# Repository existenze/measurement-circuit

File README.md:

# measurement-circuit
Measurement Circuit design for Plasma Frontiers General Atomics DIII-D Neutral Beam injector upgrade projectproject

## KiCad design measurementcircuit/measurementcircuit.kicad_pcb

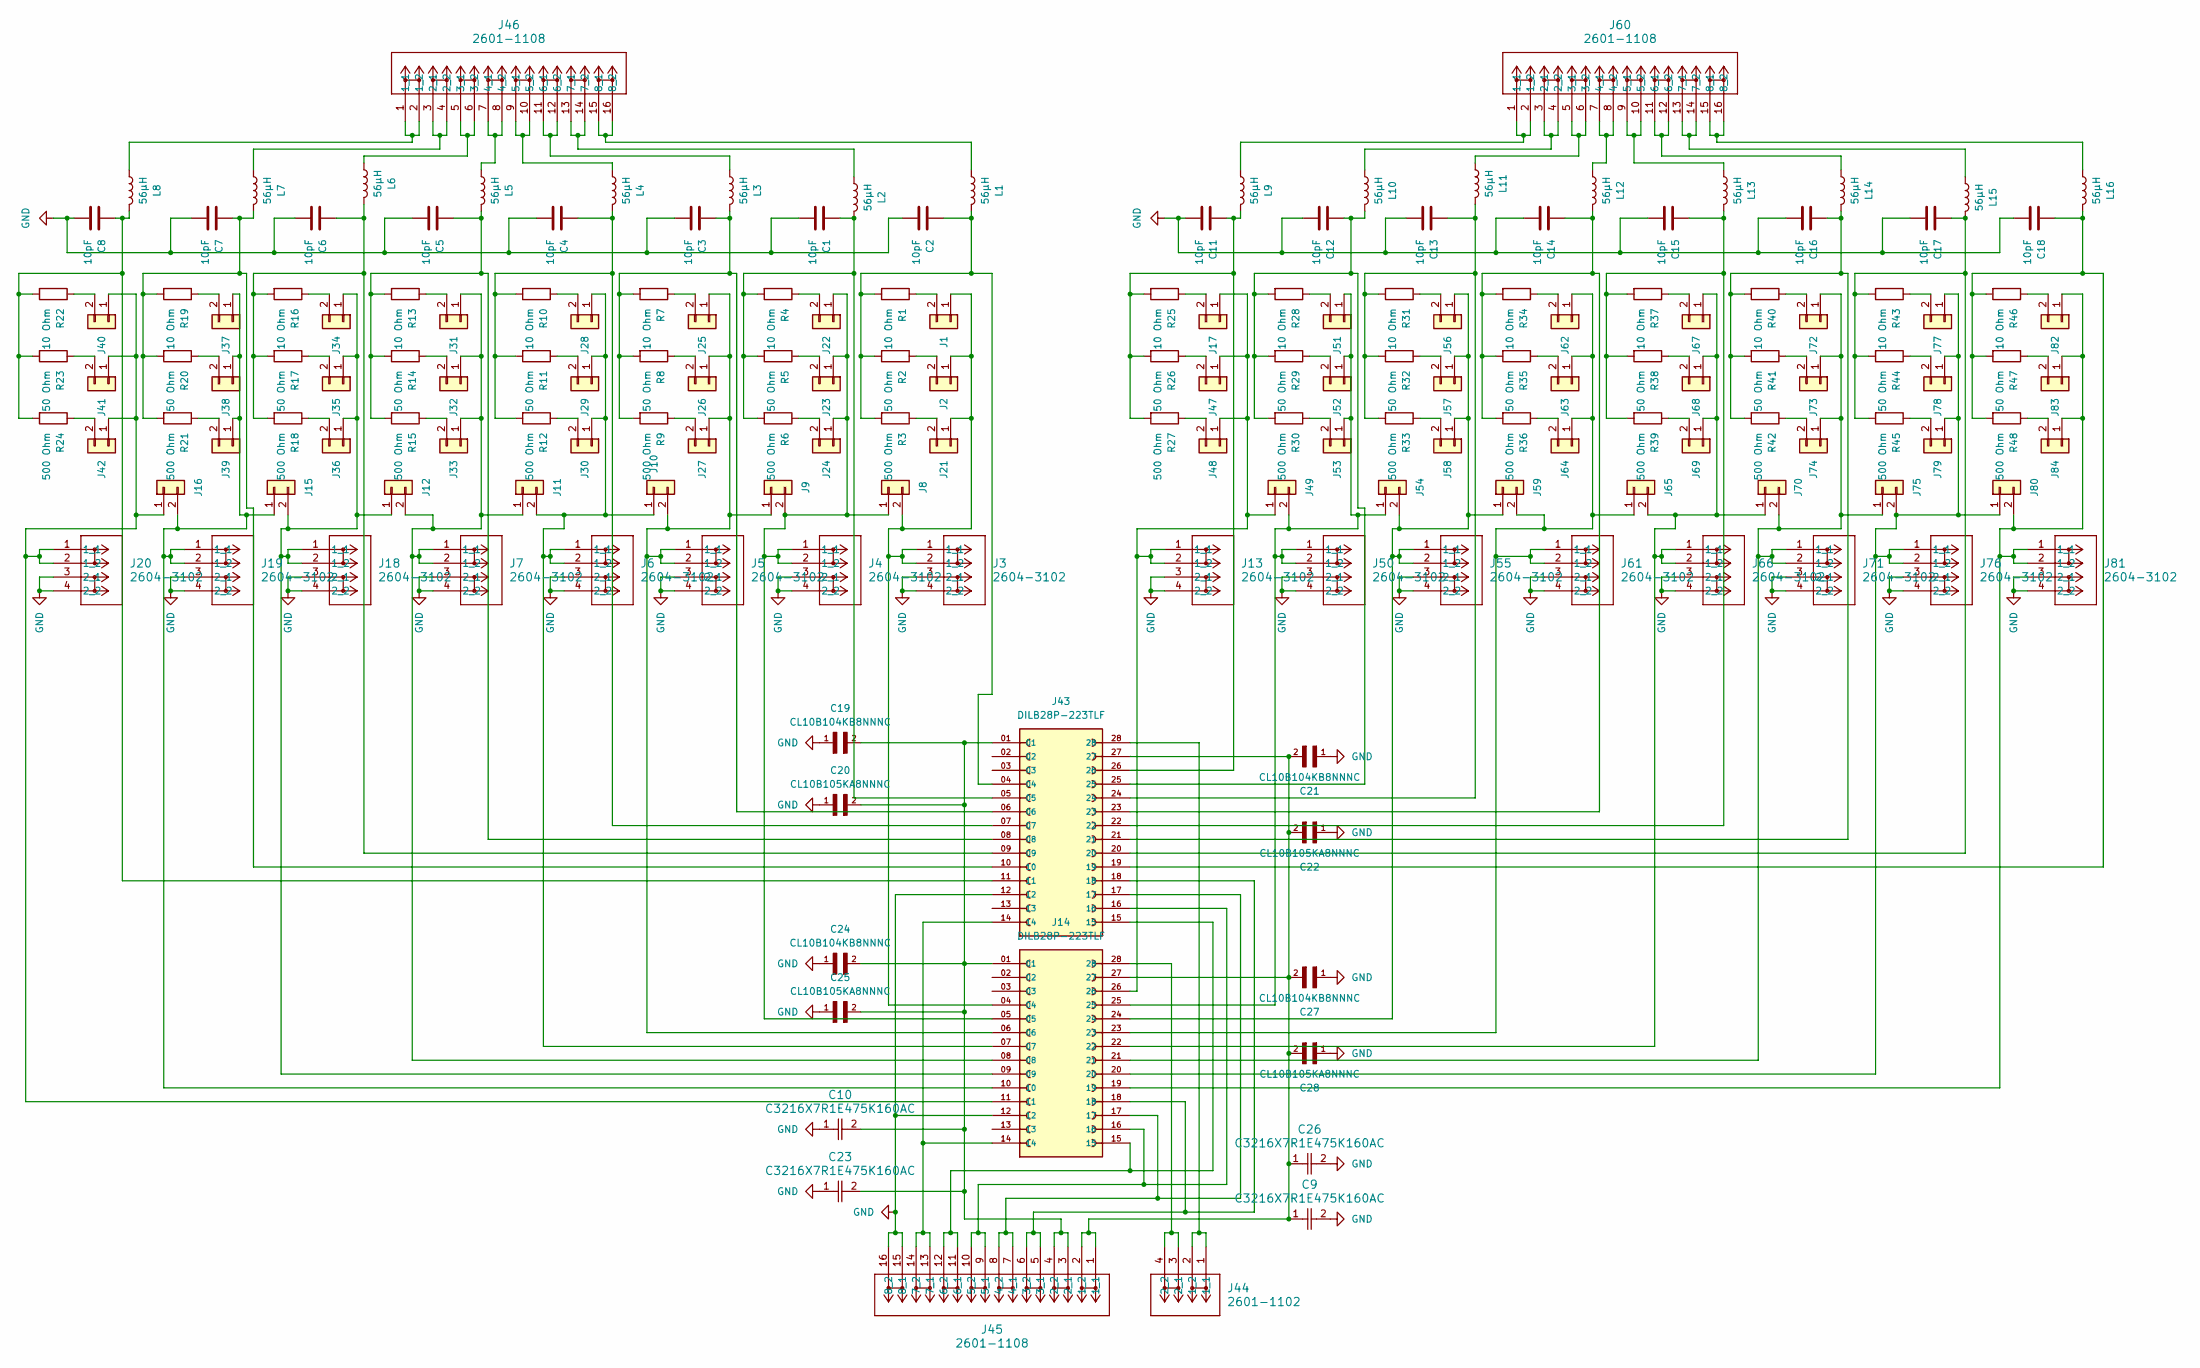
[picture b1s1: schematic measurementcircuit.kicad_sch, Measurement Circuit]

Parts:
C1, C2, C3, C4, C5, C6, C7, C8, C11, C12, C13, C14, C15, C16, C17, C18: 10pF; C_Disc_Radial_P5.90mm_W4.3mm_L11.4mm_Placeholder
C9, C10, C23, C26: C3216X7R1E475K160AC; CAP_3216_TDK
C19, C21, C24, C27: CL10B104KB8NNNC; CAPC1608X90N
C20, C22, C25, C28: CL10B105KA8NNNC; CAPC1608X90N
J1, J2, J8, J9, J10, J11, J12, J15, J16, J17, J21, J22, J23, J24, J25, J26, J27, J28, J29, J30, J31, J32, J33, J34, J35, J36, J37, J38, J39, J40, J41, J42, J47, J48, J49, J51, J52, J53, J54, J56, J57, J58, J59, J62, J63, J64, J65, J67, J68, J69, J70, J72, J73, J74, J75, J77, J78, J79, J80, J82, J83, J84: Conn_01x02; PinHeader_1x02_P2.54mm_Vertical
J3, J4, J5, J6, J7, J13, J18, J19, J20, J50, J55, J61, J66, J71, J76, J81: 2604-3102; CONN2_2601-1102_WAG
J14, J43: DILB28P-223TLF; AMPHENOL_DILB28P-223TLF; PARTREV F
J44: 2601-1102; CONN2_2601-1102_WAG
J45, J46, J60: 2601-1108; CONN8_2601-1108_WAG
L1, L2, L3, L4, L5, L6, L7, L8, L9, L10, L11, L12, L13, L14, L15, L16: 56μH; INDAD1400W80L920D650
R1, R4, R7, R10, R13, R16, R19, R22, R25, R28, R31, R34, R37, R40, R43, R46: 10 Ohm; RS010_VIS
R2, R5, R8, R11, R14, R17, R20, R23, R26, R29, R32, R35, R38, R41, R44, R47: 50 Ohm; RES_CMF60_VIS
R3, R6, R9, R12, R15, R18, R21, R24, R27, R30, R33, R36, R39, R42, R45, R48: 500 Ohm; CMF65_VIS

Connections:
GND: C1.2, C2.2, C3.2, C4.2, C5.2, C6.2, C7.2, C8.2, C9.2, C10.1, C11.2, C12.2, C13.2, C14.2, C15.2, C16.2, C17.2, C18.2, C19.1, C20.1, C21.1, C22.1, C23.1, C24.1, C25.1, C26.2, C27.1, C28.1, J3.3 (2_1), J3.4 (2_2), J4.3 (2_1), J4.4 (2_2), J5.3 (2_1), J5.4 (2_2), J6.3 (2_1), J6.4 (2_2), J7.3 (2_1), J7.4 (2_2), J13.3 (2_1), J13.4 (2_2), J14.12, J18.3 (2_1), J18.4 (2_2), J19.3 (2_1), J19.4 (2_2), J20.3 (2_1), J20.4 (2_2), J43.12, J45.15 (8_1), J45.16 (8_2), J50.3 (2_1), J50.4 (2_2), J55.3 (2_1), J55.4 (2_2), J61.3 (2_1), J61.4 (2_2), J66.3 (2_1), J66.4 (2_2), J71.3 (2_1), J71.4 (2_2), J76.3 (2_1), J76.4 (2_2), J81.3 (2_1), J81.4 (2_2)
unnamed: C1.1, J43.05, L2.2, R4.2, R5.2, R6.2
unnamed: C2.1, J43.04, L1.2, R1.2, R2.2, R3.2
unnamed: C3.1, J43.06, L3.2, R7.2, R8.2, R9.2
unnamed: C4.1, J43.07, L4.2, R10.2, R11.2, R12.2
unnamed: C5.1, J43.08, L5.2, R13.2, R14.2, R15.2
unnamed: C6.1, J43.09, L6.2, R16.2, R17.2, R18.2
unnamed: C7.1, J43.10, L7.2, R19.2, R20.2, R21.2
unnamed: C8.1, J43.11, L8.2, R22.2, R23.2, R24.2
unnamed: C11.1, J43.26, L9.2, R25.2, R26.2, R27.2
unnamed: C12.1, J43.25, L10.2, R28.2, R29.2, R30.2
unnamed: C13.1, J43.24, L11.2, R31.2, R32.2, R33.2
unnamed: C14.1, J43.23, L12.2, R34.2, R35.2, R36.2
unnamed: C15.1, J43.22, L13.2, R37.2, R38.2, R39.2
unnamed: C16.1, J43.21, L14.2, R40.2, R41.2, R42.2
unnamed: C17.1, J43.20, L15.2, R43.2, R44.2, R45.2
unnamed: C18.1, J43.19, L16.2, R46.2, R47.2, R48.2
unnamed: J1.1, J2.1, J3.1 (1_1), J3.2 (1_2), J8.2, J14.04, J21.1
unnamed: J1.2, R1.1
unnamed: J2.2, R2.1
unnamed: J6.1 (1_1), J6.2 (1_2), J10.1, J11.2, J14.07, J28.1, J29.1, J30.1
unnamed: J5.1 (1_1), J5.2 (1_2), J9.1, J10.2, J14.06, J25.1, J26.1, J27.1
unnamed: J7.1 (1_1), J7.2 (1_2), J11.1, J12.2, J14.08, J31.1, J32.1, J33.1
unnamed: J12.1, J14.09, J15.2, J18.1 (1_1), J18.2 (1_2), J34.1, J35.1, J36.1
unnamed: J13.1 (1_1), J13.2 (1_2), J14.26, J17.1, J47.1, J48.1, J49.1
unnamed: J14.10, J15.1, J16.2, J19.1 (1_1), J19.2 (1_2), J37.1, J38.1, J39.1
unnamed: J14.11, J16.1, J20.1 (1_1), J20.2 (1_2), J40.1, J41.1, J42.1
unnamed: J17.2, R25.1
unnamed: J21.2, R3.1
unnamed: J4.1 (1_1), J4.2 (1_2), J8.1, J9.2, J14.05, J22.1, J23.1, J24.1
unnamed: J22.2, R4.1
unnamed: J23.2, R5.1
unnamed: J24.2, R6.1
unnamed: J25.2, R7.1
unnamed: J26.2, R8.1
unnamed: J27.2, R9.1
unnamed: J28.2, R10.1
unnamed: J29.2, R11.1
unnamed: J30.2, R12.1
unnamed: J31.2, R13.1
unnamed: J32.2, R14.1
unnamed: J33.2, R15.1
unnamed: J34.2, R16.1
unnamed: J35.2, R17.1
unnamed: J36.2, R18.1
unnamed: J37.2, R19.1
unnamed: J38.2, R20.1
unnamed: J39.2, R21.1
unnamed: J40.2, R22.1
unnamed: J41.2, R23.1
unnamed: J42.2, R24.1
unnamed: J43.28, J44.1 (1_1), J44.2 (1_2)
unnamed: J14.28, J44.3 (2_1), J44.4 (2_2)
unnamed: C9.1, C21.2, C22.2, C26.1, C27.2, C28.2, J14.27, J43.27, J45.1 (1_1), J45.2 (1_2)
unnamed: C10.2, C19.2, C20.2, C23.2, C24.2, C25.2, J14.01, J43.01, J45.3 (2_1), J45.4 (2_2)
unnamed: J14.18, J43.18, J45.5 (3_1), J45.6 (3_2)
unnamed: J14.17, J43.17, J45.7 (4_1), J45.8 (4_2)
unnamed: J14.16, J43.16, J45.9 (5_1), J45.10 (5_2)
unnamed: J14.15, J43.15, J45.11 (6_1), J45.12 (6_2)
unnamed: J14.14, J43.14, J45.13 (7_1), J45.14 (7_2)
unnamed: J46.1 (1_1), J46.2 (1_2), L8.1
unnamed: J46.3 (2_1), J46.4 (2_2), L7.1
unnamed: J46.5 (3_1), J46.6 (3_2), L6.1
unnamed: J46.7 (4_1), J46.8 (4_2), L5.1
unnamed: J46.9 (5_1), J46.10 (5_2), L4.1
unnamed: J46.11 (6_1), J46.12 (6_2), L3.1
unnamed: J46.13 (7_1), J46.14 (7_2), L2.1
unnamed: J46.15 (8_1), J46.16 (8_2), L1.1
unnamed: J47.2, R26.1
unnamed: J48.2, R27.1
unnamed: J14.25, J49.2, J50.1 (1_1), J50.2 (1_2), J51.1, J52.1, J53.1, J54.1
unnamed: J51.2, R28.1
unnamed: J52.2, R29.1
unnamed: J53.2, R30.1
unnamed: J14.24, J54.2, J55.1 (1_1), J55.2 (1_2), J56.1, J57.1, J58.1, J59.1
unnamed: J56.2, R31.1
unnamed: J57.2, R32.1
unnamed: J58.2, R33.1
unnamed: J14.23, J59.2, J61.1 (1_1), J61.2 (1_2), J62.1, J63.1, J64.1, J65.1
unnamed: J60.1 (1_1), J60.2 (1_2), L9.1
unnamed: J60.3 (2_1), J60.4 (2_2), L10.1
unnamed: J60.5 (3_1), J60.6 (3_2), L11.1
unnamed: J60.7 (4_1), J60.8 (4_2), L12.1
unnamed: J60.9 (5_1), J60.10 (5_2), L13.1
unnamed: J60.11 (6_1), J60.12 (6_2), L14.1
unnamed: J60.13 (7_1), J60.14 (7_2), L15.1
unnamed: J60.15 (8_1), J60.16 (8_2), L16.1
unnamed: J62.2, R34.1
unnamed: J63.2, R35.1
unnamed: J64.2, R36.1
unnamed: J14.22, J65.2, J66.1 (1_1), J66.2 (1_2), J67.1, J68.1, J69.1, J70.1
unnamed: J67.2, R37.1
unnamed: J68.2, R38.1
unnamed: J69.2, R39.1
unnamed: J14.21, J70.2, J71.1 (1_1), J71.2 (1_2), J72.1, J73.1, J74.1, J75.1
unnamed: J72.2, R40.1
unnamed: J73.2, R41.1
unnamed: J74.2, R42.1
unnamed: J14.20, J75.2, J76.1 (1_1), J76.2 (1_2), J77.1, J78.1, J79.1, J80.1
unnamed: J77.2, R43.1
unnamed: J78.2, R44.1
unnamed: J79.2, R45.1
unnamed: J14.19, J80.2, J81.1 (1_1), J81.2 (1_2), J82.1, J83.1, J84.1
unnamed: J82.2, R46.1
unnamed: J83.2, R47.1
unnamed: J84.2, R48.1

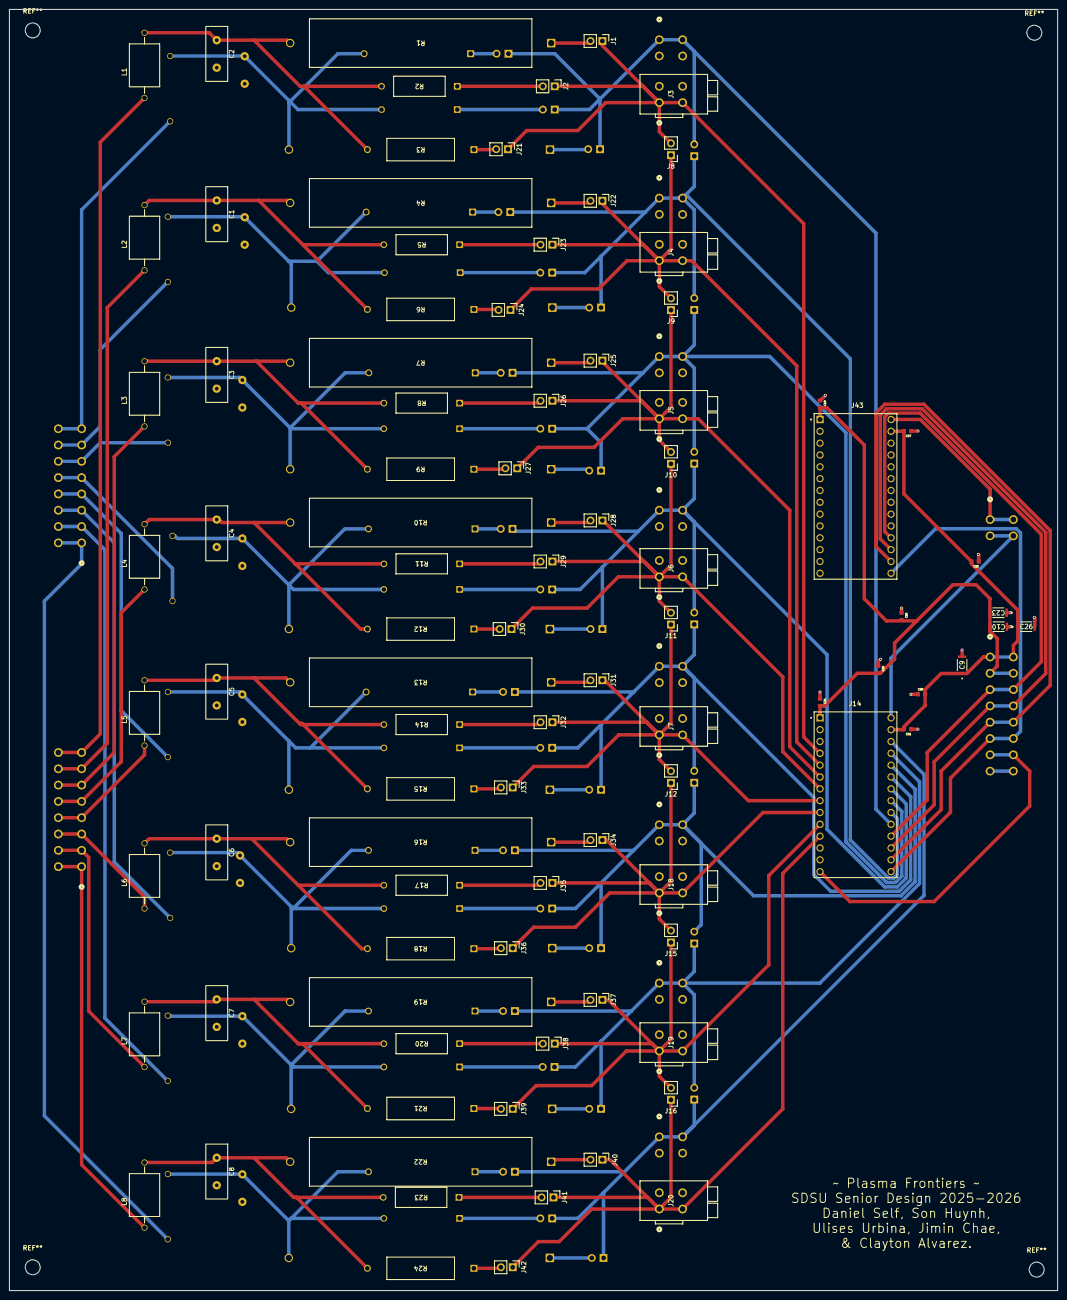
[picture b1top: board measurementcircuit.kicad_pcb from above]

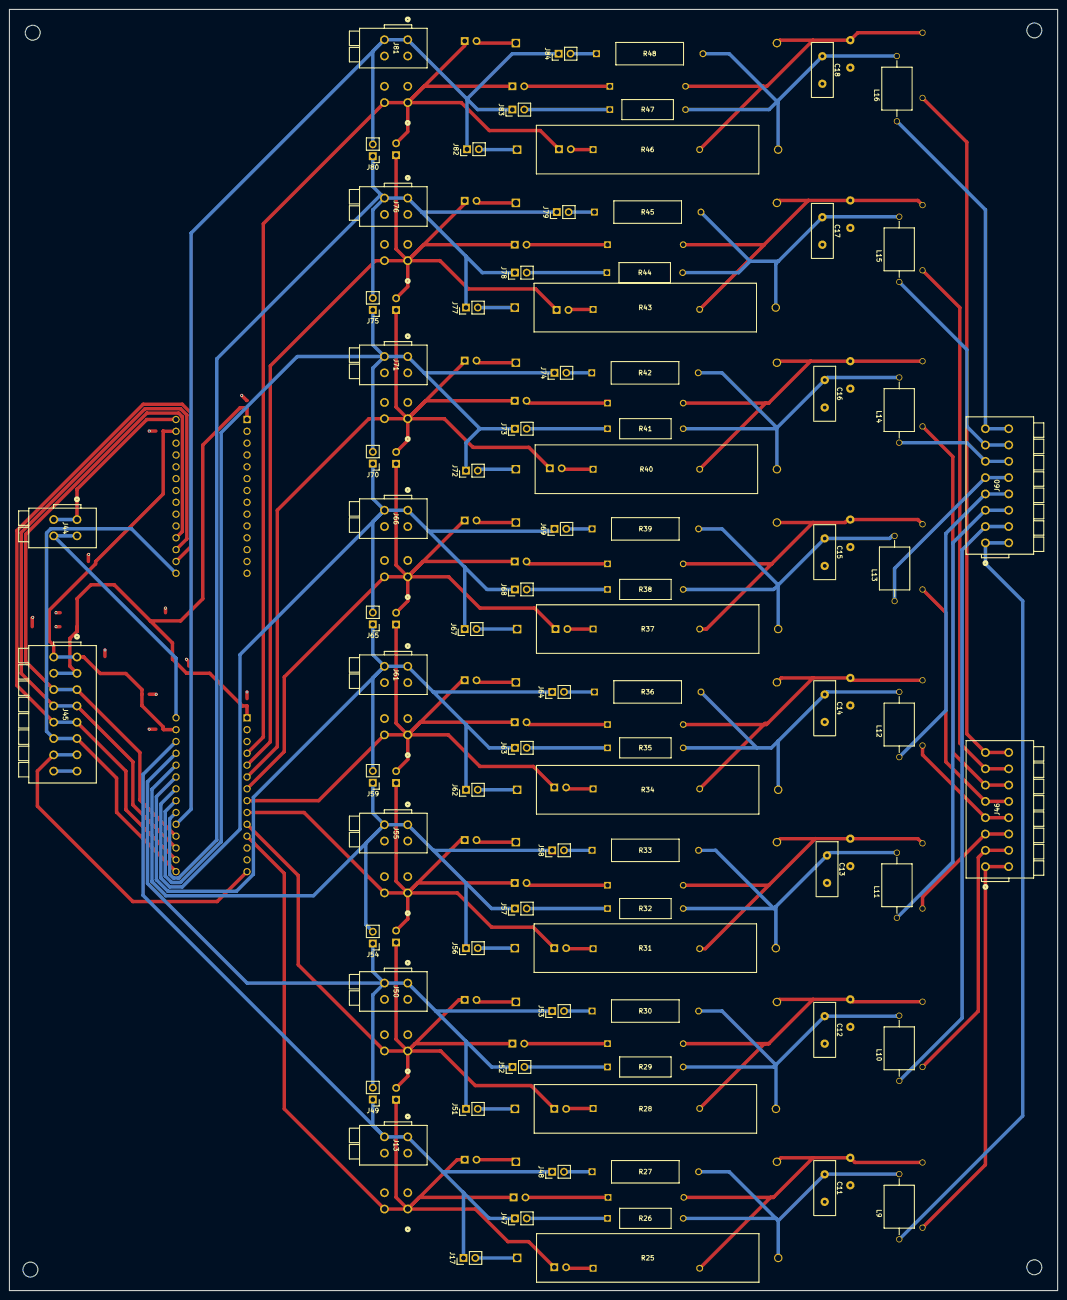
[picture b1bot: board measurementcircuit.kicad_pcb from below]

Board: 4 copper layers, 225.0 x 275.0 mm, 176 parts (83 on the bottom side), 106 nets.

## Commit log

2025-10-15 Create KiCad measurement files
2025-10-15 test
2025-11-06 Only missing POT
2025-11-06 Did some of the PCB layout
2025-11-07 Added Clamp FIles
    Includes schematic symbol, footprint, and 3D model.
2025-11-10 Pull/update
2025-11-16 Daniel Measurement Circuit Work
    Add more routes to make a total of 8 circuits, component selections and placement, routing, finish schematic and pcb design. Switched back to 3 different circuits with shunts. Just need to fix some i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
2025-11-17 Fix traces after rearrangement of measurement schematic
2025-11-17 cleanup for CDR
    traces wider, etc
2025-12-09 Update
    most up to date circuit
2025-12-14 Resize canvas
2025-12-15 Edit random dots out
2025-12-15 Save changes
2025-12-15 Change footprints/cad and move into repo
    start with connectors moving onto others next
2025-12-18 update before new work since 12/16 sponsor meeting
2025-12-19 update before new design work
2025-12-21 First Redesign Changes
    Switch to 4-layer PCB with inner copper layers as ground layers for top and bottom. Add holes for standoffs. Clockwise orientation of schematic to accommodate double the channels.
2025-12-21 Redesign Work - Symbols, Schematic Overhaul
2025-12-21 Schematic Complete
2025-12-21 Add Decoupling Caps and Local Bulk Caps for VDD and VSS rails
2025-12-21 Figured out Bottom layer placement, some footprint changes
2025-12-22 Add footprints, reassign footprints, change power supply connectors to new 2-pole style
2025-12-22 PCB work, footing placement
2025-12-22 Place Resistors, other footprint placements
2025-12-22 Save before drawing traces
2025-12-22 Major PCB work, Ready for review
    Still need to reassign 3D models
2025-12-22 Finish PCB, Schematic and PCB ready for review
2025-12-23 Add Standoff Mounting M3 Holes
2026-02-01 Update before switching to Daniel Branch
2026-02-01 update before working
